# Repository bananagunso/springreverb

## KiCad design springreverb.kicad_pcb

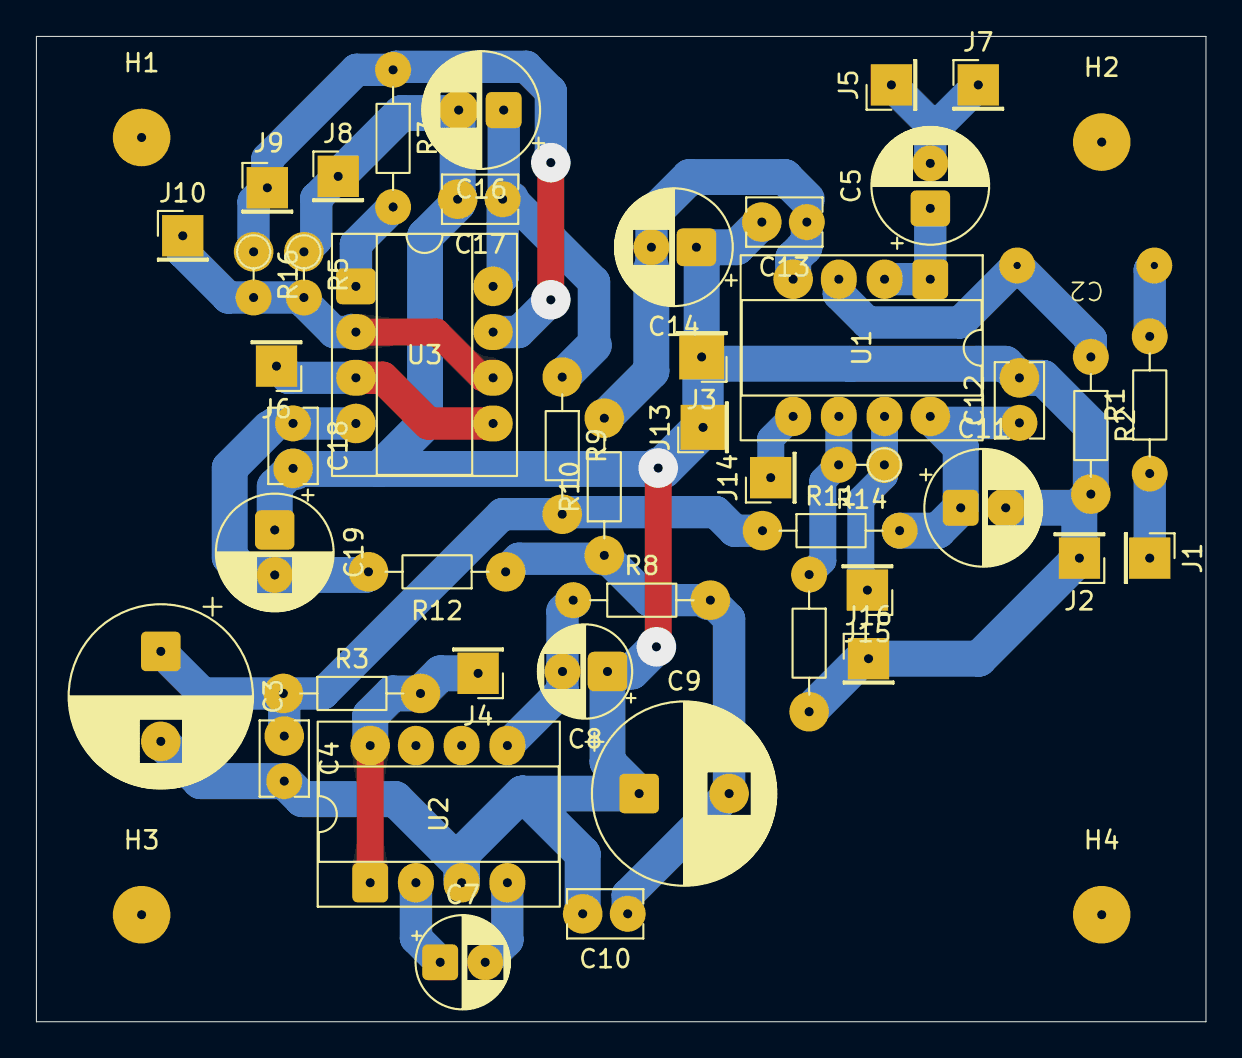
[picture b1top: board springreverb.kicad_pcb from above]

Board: 2 copper layers, 65.0 x 54.7 mm, 50 parts (0 on the bottom side), 23 nets.

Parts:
C2: 0.1u; 10.5_5.0_p7.5
C3, C9: 1000u; CP_Radial_D10.0mm_P5.00mm
C4, C10, C12, C13, C17, C18: 0.1u; C_Rect_L4.0mm_W2.5mm_P2.50mm
C5, C11, C14, C16, C19: 100u; CP_Radial_D6.3mm_P2.50mm
C7, C8: 10u; CP_Radial_D5.0mm_P2.50mm
H1, H2, H3, H4: MountingHole; MountingHole_3.2mm_M3
J1: IN; PinHeader_1x01_P2.54mm_Vertical
J2: INGND; PinHeader_1x01_P2.54mm_Vertical
J3: GND; PinHeader_1x01_P2.54mm_Vertical
J4: Vin; PinHeader_1x01_P2.54mm_Vertical
J5: VR1_3; PinHeader_1x01_P2.54mm_Vertical
J6: VR1_2; PinHeader_1x01_P2.54mm_Vertical
J7: VR3_1; PinHeader_1x01_P2.54mm_Vertical
J8: ToGND; PinHeader_1x01_P2.54mm_Vertical
J9: To; PinHeader_1x01_P2.54mm_Vertical
J10: To2; PinHeader_1x01_P2.54mm_Vertical
J13: FromGND; PinHeader_1x01_P2.54mm_Vertical
J14: From; PinHeader_1x01_P2.54mm_Vertical
J15: VR2_3; PinHeader_1x01_P2.54mm_Vertical
J16: VR2_3GND; PinHeader_1x01_P2.54mm_Vertical
R1: 10k; R_Axial_DIN0204_L3.6mm_D1.6mm_P7.62mm_Horizontal
R2: 1M; R_Axial_DIN0204_L3.6mm_D1.6mm_P7.62mm_Horizontal
R3, R7, R8: 10; R_Axial_DIN0204_L3.6mm_D1.6mm_P7.62mm_Horizontal
R5: 1.2k; R_Axial_DIN0204_L3.6mm_D1.6mm_P2.54mm_Vertical
R9: 100; R_Axial_DIN0204_L3.6mm_D1.6mm_P7.62mm_Horizontal
R10, R11: 470; R_Axial_DIN0204_L3.6mm_D1.6mm_P7.62mm_Horizontal
R12: 47; R_Axial_DIN0204_L3.6mm_D1.6mm_P7.62mm_Horizontal
R13: 2.2k; R_Axial_DIN0204_L3.6mm_D1.6mm_P7.62mm_Horizontal
R14: 220k; R_Axial_DIN0204_L3.6mm_D1.6mm_P2.54mm_Vertical
R16: 1k; R_Axial_DIN0204_L3.6mm_D1.6mm_P2.54mm_Vertical
U1: TL072; CERDIP-8_W7.62mm_SideBrazed_Socket
U2: TC1044S; CERDIP-8_W7.62mm_SideBrazed_Socket
U3: 4556ADD; CERDIP-8_W7.62mm_SideBrazed_Socket

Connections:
GND: C3.2, C4.2, C8.1, C9.1, C10.2, C11.2, C12.2, C13.2, C14.1, C16.2, C17.2, C18.2, C19.1, J2.1, J3.1, J8.1, J13.1, J16.1, R2.2, R5.1, R13.2, U2.3 (GND)
unnamed: C2.1, R1.2
unnamed: C3.1, C4.1, R3.1, R9.2, R11.1
unnamed: C9.2, C10.1, R8.2, R10.1, R12.1
unnamed: J1.1, R1.1
unnamed: J4.1, R3.2, U2.1 (BOOST), U2.8 (V+)
unnamed: C5.2, J5.1, J7.1
unnamed: J6.1, U3.3 (+), U3.5 (+)
unnamed: J10.1, R5.2, R16.2, U3.2 (-), U3.6 (-)
unnamed: J9.1, R7.1, R16.1, U3.7
unnamed: J14.1, U1.5 (+)
unnamed: J15.1, R14.1, U1.7
unnamed: R7.2, U3.1
unnamed: C2.2, R2.1, U1.3 (+)
unnamed: C5.1, U1.1, U1.2 (-)
unnamed: R13.1, R14.2, U1.6 (-)
unnamed: C11.1, C12.1, R11.2, U1.8 (V+)
unnamed: C13.1, C14.2, R10.2, U1.4 (V-)
unnamed: C7.1, U2.2 (CAP+)
unnamed: C7.2, U2.4 (CAP-)
unnamed: C8.2, R8.1, U2.5 (VOUT)
unnamed: C16.1, C17.1, R9.1, U3.8 (V+)
unnamed: C18.1, C19.2, R12.2, U3.4 (V-)

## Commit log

2026-03-27 スプリングリバーブ作り直す
2026-04-02 配置修整
2026-04-07 部品を配置した
2026-04-07 フラグを追加
2026-04-07 表示の修正
2026-04-09 配線のクリアランスを0.4にして修正
2026-04-13 ボリュームのつなぎ方とか色々修正
2026-04-13 ドライブ段の回路がおかしかった
2026-04-13 発振対策とVPの接続先を修正
2026-04-14 増幅率やVR1とC5の前後を入れ替えたり
